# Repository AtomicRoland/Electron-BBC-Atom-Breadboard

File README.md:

# Electron-BBC-Atom-Breadboard
For simple circuits or just for testing purposes you can use this bread board for the Acorn Electron (via a Plus1 cartridge slot) or the BBC / Master / Atom (with 1 MHz bus conversion board). The board has four banks of five rows with 36 pins each.

There are connections between the User port socket and user port holes, between the 1 MHz bus socket and the 1 MHz bus holes and between the edge connector and the 44 holes for the Electron Plus1 cartridge slot.
Optionally you can add a 44 pin header so the board can be connected to the Electron break-out and riser board (but this generally only works reliable for I/O devices running at 1 MHz; ROMS accessed at 2 MHz might fail). Also eight SMD leds with series resistors can be added. The leds are not connected to Vcc or GND so you can use both active high and active low levels to control the leds. 

Of course you can also use this break out board without the female header strips to build a permanent circuit if you have a simple design in mind. That save you the trouble of creating a printed circuit board.
                                                 
*Please unzip the myelin-kicad.pretty-master.zip file before opening the project in KiCad*

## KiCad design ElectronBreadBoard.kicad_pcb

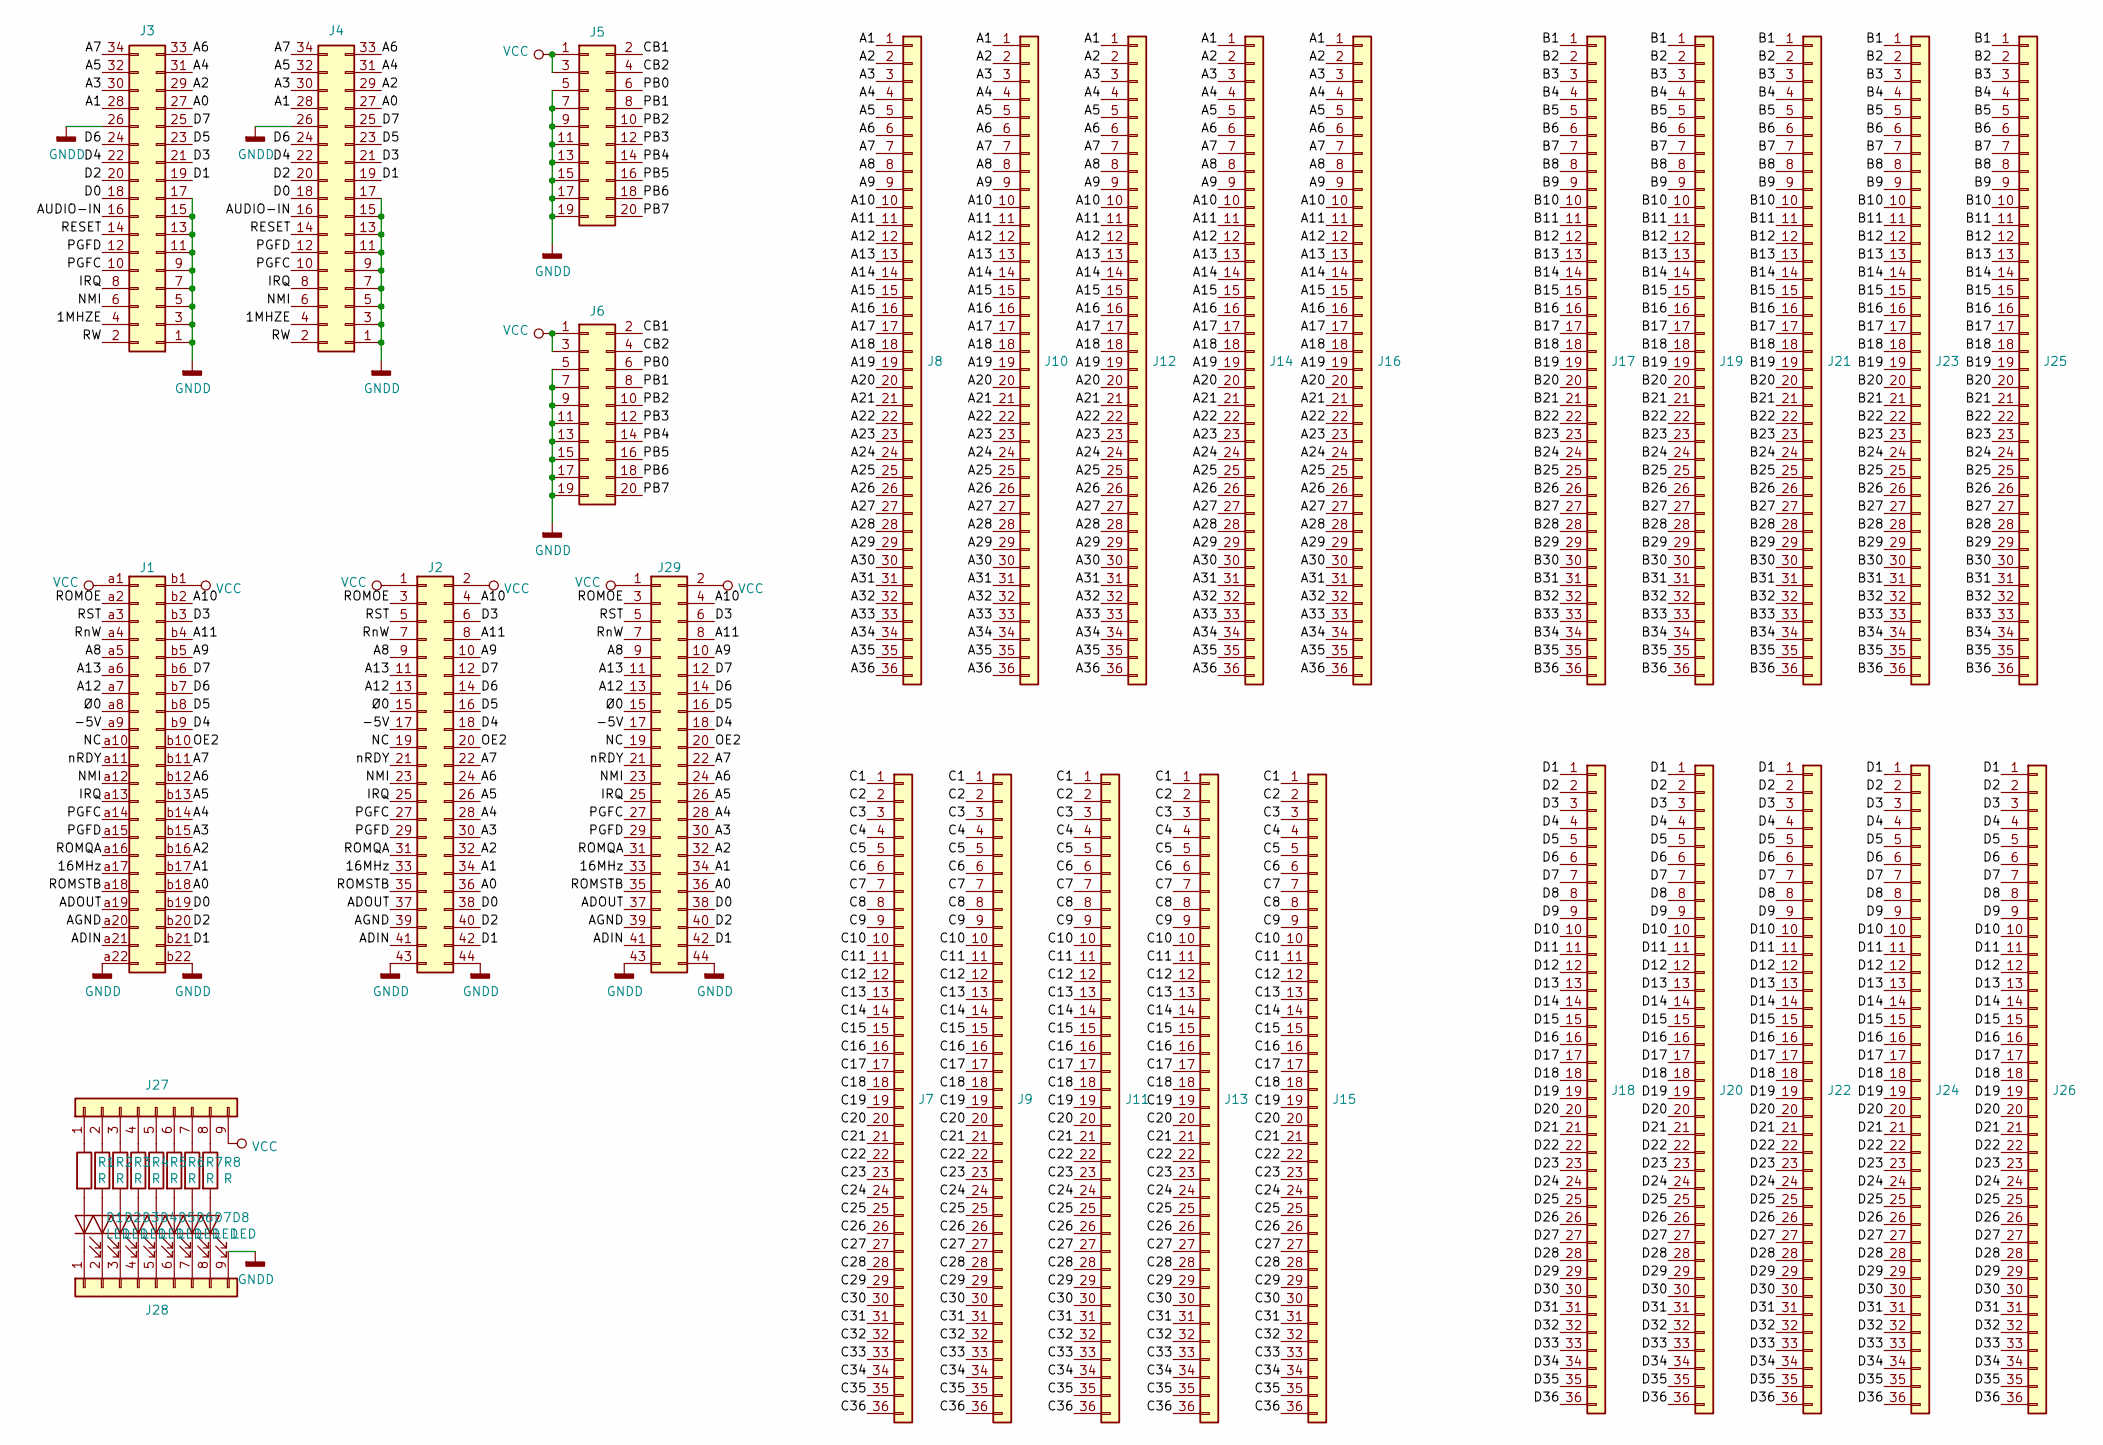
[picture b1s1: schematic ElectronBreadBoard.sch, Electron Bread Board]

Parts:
D1, D2, D3, D4, D5, D6, D7, D8: LED; D_1206_3216Metric_Pad1.42x1.75mm_HandSolder
J1: Conn_02x22_Row_Letter_First; acorn_electron_cartridge_edge_connector
J2, J29: Conn_02x22_Odd_Even; PinHeader_2x22_P2.54mm_Vertical
J3, J4: Conn_02x17_Odd_Even; PinHeader_2x17_P2.54mm_Vertical
J5, J6: Conn_02x10_Odd_Even; PinHeader_2x10_P2.54mm_Vertical
J7, J8, J9, J10, J11, J12, J13, J14, J15, J16, J17, J18, J19, J20, J21, J22, J23, J24, J25, J26: Conn_01x36; PinHeader_1x36_P2.54mm_Vertical
J27, J28: Conn_01x09; PinHeader_1x09_P2.54mm_Vertical
R1, R2, R3, R4, R5, R6, R7, R8: R; R_1206_3216Metric_Pad1.42x1.75mm_HandSolder

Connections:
/1MHZE: J3.4, J4.4
/16MHz: J1.a17, J2.33, J29.33
/-5V: J1.a9, J2.17, J29.17
/A0: J1.b18, J2.36, J3.27, J4.27, J29.36
/A1: J1.b17, J2.34, J3.28, J4.28, J8.1, J10.1, J12.1, J14.1, J16.1, J29.34
/A2: J1.b16, J2.32, J3.29, J4.29, J8.2, J10.2, J12.2, J14.2, J16.2, J29.32
/A3: J1.b15, J2.30, J3.30, J4.30, J8.3, J10.3, J12.3, J14.3, J16.3, J29.30
/A4: J1.b14, J2.28, J3.31, J4.31, J8.4, J10.4, J12.4, J14.4, J16.4, J29.28
/A5: J1.b13, J2.26, J3.32, J4.32, J8.5, J10.5, J12.5, J14.5, J16.5, J29.26
/A6: J1.b12, J2.24, J3.33, J4.33, J8.6, J10.6, J12.6, J14.6, J16.6, J29.24
/A7: J1.b11, J2.22, J3.34, J4.34, J8.7, J10.7, J12.7, J14.7, J16.7, J29.22
/A8: J1.a5, J2.9, J8.8, J10.8, J12.8, J14.8, J16.8, J29.9
/A9: J1.b5, J2.10, J8.9, J10.9, J12.9, J14.9, J16.9, J29.10
/A10: J1.b2, J2.4, J8.10, J10.10, J12.10, J14.10, J16.10, J29.4
/A11: J1.b4, J2.8, J8.11, J10.11, J12.11, J14.11, J16.11, J29.8
/A12: J1.a7, J2.13, J8.12, J10.12, J12.12, J14.12, J16.12, J29.13
/A13: J1.a6, J2.11, J8.13, J10.13, J12.13, J14.13, J16.13, J29.11
/A14: J8.14, J10.14, J12.14, J14.14, J16.14
/A15: J8.15, J10.15, J12.15, J14.15, J16.15
/A16: J8.16, J10.16, J12.16, J14.16, J16.16
/A17: J8.17, J10.17, J12.17, J14.17, J16.17
/A18: J8.18, J10.18, J12.18, J14.18, J16.18
/A19: J8.19, J10.19, J12.19, J14.19, J16.19
/A20: J8.20, J10.20, J12.20, J14.20, J16.20
/A21: J8.21, J10.21, J12.21, J14.21, J16.21
/A22: J8.22, J10.22, J12.22, J14.22, J16.22
/A23: J8.23, J10.23, J12.23, J14.23, J16.23
/A24: J8.24, J10.24, J12.24, J14.24, J16.24
/A25: J8.25, J10.25, J12.25, J14.25, J16.25
/A26: J8.26, J10.26, J12.26, J14.26, J16.26
/A27: J8.27, J10.27, J12.27, J14.27, J16.27
/A28: J8.28, J10.28, J12.28, J14.28, J16.28
/A29: J8.29, J10.29, J12.29, J14.29, J16.29
/A30: J8.30, J10.30, J12.30, J14.30, J16.30
/A31: J8.31, J10.31, J12.31, J14.31, J16.31
/A32: J8.32, J10.32, J12.32, J14.32, J16.32
/A33: J8.33, J10.33, J12.33, J14.33, J16.33
/A34: J8.34, J10.34, J12.34, J14.34, J16.34
/A35: J8.35, J10.35, J12.35, J14.35, J16.35
/A36: J8.36, J10.36, J12.36, J14.36, J16.36
/ADIN: J1.a21, J2.41, J29.41
/ADOUT: J1.a19, J2.37, J29.37
/AGND: J1.a20, J2.39, J29.39
/AUDIO-IN: J3.16, J4.16
/B1: J17.1, J19.1, J21.1, J23.1, J25.1
/B2: J17.2, J19.2, J21.2, J23.2, J25.2
/B3: J17.3, J19.3, J21.3, J23.3, J25.3
/B4: J17.4, J19.4, J21.4, J23.4, J25.4
/B5: J17.5, J19.5, J21.5, J23.5, J25.5
/B6: J17.6, J19.6, J21.6, J23.6, J25.6
/B7: J17.7, J19.7, J21.7, J23.7, J25.7
/B8: J17.8, J19.8, J21.8, J23.8, J25.8
/B9: J17.9, J19.9, J21.9, J23.9, J25.9
/B10: J17.10, J19.10, J21.10, J23.10, J25.10
/B11: J17.11, J19.11, J21.11, J23.11, J25.11
/B12: J17.12, J19.12, J21.12, J23.12, J25.12
/B13: J17.13, J19.13, J21.13, J23.13, J25.13
/B14: J17.14, J19.14, J21.14, J23.14, J25.14
/B15: J17.15, J19.15, J21.15, J23.15, J25.15
/B16: J17.16, J19.16, J21.16, J23.16, J25.16
/B17: J17.17, J19.17, J21.17, J23.17, J25.17
/B18: J17.18, J19.18, J21.18, J23.18, J25.18
/B19: J17.19, J19.19, J21.19, J23.19, J25.19
/B20: J17.20, J19.20, J21.20, J23.20, J25.20
/B21: J17.21, J19.21, J21.21, J23.21, J25.21
/B22: J17.22, J19.22, J21.22, J23.22, J25.22
/B23: J17.23, J19.23, J21.23, J23.23, J25.23
/B24: J17.24, J19.24, J21.24, J23.24, J25.24
/B25: J17.25, J19.25, J21.25, J23.25, J25.25
/B26: J17.26, J19.26, J21.26, J23.26, J25.26
/B27: J17.27, J19.27, J21.27, J23.27, J25.27
/B28: J17.28, J19.28, J21.28, J23.28, J25.28
/B29: J17.29, J19.29, J21.29, J23.29, J25.29
/B30: J17.30, J19.30, J21.30, J23.30, J25.30
/B31: J17.31, J19.31, J21.31, J23.31, J25.31
/B32: J17.32, J19.32, J21.32, J23.32, J25.32
/B33: J17.33, J19.33, J21.33, J23.33, J25.33
/B34: J17.34, J19.34, J21.34, J23.34, J25.34
/B35: J17.35, J19.35, J21.35, J23.35, J25.35
/B36: J17.36, J19.36, J21.36, J23.36, J25.36
/C1: J7.1, J9.1, J11.1, J13.1, J15.1
/C2: J7.2, J9.2, J11.2, J13.2, J15.2
/C3: J7.3, J9.3, J11.3, J13.3, J15.3
/C4: J7.4, J9.4, J11.4, J13.4, J15.4
/C5: J7.5, J9.5, J11.5, J13.5, J15.5
/C6: J7.6, J9.6, J11.6, J13.6, J15.6
/C7: J7.7, J9.7, J11.7, J13.7, J15.7
/C8: J7.8, J9.8, J11.8, J13.8, J15.8
/C9: J7.9, J9.9, J11.9, J13.9, J15.9
/C10: J7.10, J9.10, J11.10, J13.10, J15.10
/C11: J7.11, J9.11, J11.11, J13.11, J15.11
/C12: J7.12, J9.12, J11.12, J13.12, J15.12
/C13: J7.13, J9.13, J11.13, J13.13, J15.13
/C14: J7.14, J9.14, J11.14, J13.14, J15.14
/C15: J7.15, J9.15, J11.15, J13.15, J15.15
/C16: J7.16, J9.16, J11.16, J13.16, J15.16
/C17: J7.17, J9.17, J11.17, J13.17, J15.17
/C18: J7.18, J9.18, J11.18, J13.18, J15.18
/C19: J7.19, J9.19, J11.19, J13.19, J15.19
/C20: J7.20, J9.20, J11.20, J13.20, J15.20
/C21: J7.21, J9.21, J11.21, J13.21, J15.21
/C22: J7.22, J9.22, J11.22, J13.22, J15.22
/C23: J7.23, J9.23, J11.23, J13.23, J15.23
/C24: J7.24, J9.24, J11.24, J13.24, J15.24
/C25: J7.25, J9.25, J11.25, J13.25, J15.25
/C26: J7.26, J9.26, J11.26, J13.26, J15.26
/C27: J7.27, J9.27, J11.27, J13.27, J15.27
/C28: J7.28, J9.28, J11.28, J13.28, J15.28
/C29: J7.29, J9.29, J11.29, J13.29, J15.29
/C30: J7.30, J9.30, J11.30, J13.30, J15.30
/C31: J7.31, J9.31, J11.31, J13.31, J15.31
/C32: J7.32, J9.32, J11.32, J13.32, J15.32
/C33: J7.33, J9.33, J11.33, J13.33, J15.33
/C34: J7.34, J9.34, J11.34, J13.34, J15.34
/C35: J7.35, J9.35, J11.35, J13.35, J15.35
/C36: J7.36, J9.36, J11.36, J13.36, J15.36
/CB1: J5.2, J6.2
/CB2: J5.4, J6.4
/D0: J1.b19, J2.38, J3.18, J4.18, J29.38
/D1: J1.b21, J2.42, J3.19, J4.19, J18.1, J20.1, J22.1, J24.1, J26.1, J29.42
/D2: J1.b20, J2.40, J3.20, J4.20, J18.2, J20.2, J22.2, J24.2, J26.2, J29.40
/D3: J1.b3, J2.6, J3.21, J4.21, J18.3, J20.3, J22.3, J24.3, J26.3, J29.6
/D4: J1.b9, J2.18, J3.22, J4.22, J18.4, J20.4, J22.4, J24.4, J26.4, J29.18
/D5: J1.b8, J2.16, J3.23, J4.23, J18.5, J20.5, J22.5, J24.5, J26.5, J29.16
/D6: J1.b7, J2.14, J3.24, J4.24, J18.6, J20.6, J22.6, J24.6, J26.6, J29.14
/D7: J1.b6, J2.12, J3.25, J4.25, J18.7, J20.7, J22.7, J24.7, J26.7, J29.12
/D8: J18.8, J20.8, J22.8, J24.8, J26.8
/D9: J18.9, J20.9, J22.9, J24.9, J26.9
/D10: J18.10, J20.10, J22.10, J24.10, J26.10
/D11: J18.11, J20.11, J22.11, J24.11, J26.11
/D12: J18.12, J20.12, J22.12, J24.12, J26.12
/D13: J18.13, J20.13, J22.13, J24.13, J26.13
/D14: J18.14, J20.14, J22.14, J24.14, J26.14
/D15: J18.15, J20.15, J22.15, J24.15, J26.15
/D16: J18.16, J20.16, J22.16, J24.16, J26.16
/D17: J18.17, J20.17, J22.17, J24.17, J26.17
/D18: J18.18, J20.18, J22.18, J24.18, J26.18
/D19: J18.19, J20.19, J22.19, J24.19, J26.19
/D20: J18.20, J20.20, J22.20, J24.20, J26.20
/D21: J18.21, J20.21, J22.21, J24.21, J26.21
/D22: J18.22, J20.22, J22.22, J24.22, J26.22
/D23: J18.23, J20.23, J22.23, J24.23, J26.23
/D24: J18.24, J20.24, J22.24, J24.24, J26.24
/D25: J18.25, J20.25, J22.25, J24.25, J26.25
/D26: J18.26, J20.26, J22.26, J24.26, J26.26
/D27: J18.27, J20.27, J22.27, J24.27, J26.27
/D28: J18.28, J20.28, J22.28, J24.28, J26.28
/D29: J18.29, J20.29, J22.29, J24.29, J26.29
/D30: J18.30, J20.30, J22.30, J24.30, J26.30
/D31: J18.31, J20.31, J22.31, J24.31, J26.31
/D32: J18.32, J20.32, J22.32, J24.32, J26.32
/D33: J18.33, J20.33, J22.33, J24.33, J26.33
/D34: J18.34, J20.34, J22.34, J24.34, J26.34
/D35: J18.35, J20.35, J22.35, J24.35, J26.35
/D36: J18.36, J20.36, J22.36, J24.36, J26.36
/IRQ: J1.a13, J2.25, J3.8, J4.8, J29.25
/NC: J1.a10, J2.19, J29.19
/NMI: J1.a12, J2.23, J3.6, J4.6, J29.23
/OE2: J1.b10, J2.20, J29.20
/PB0: J5.6, J6.6
/PB1: J5.8, J6.8
/PB2: J5.10, J6.10
/PB3: J5.12, J6.12
/PB4: J5.14, J6.14
/PB5: J5.16, J6.16
/PB6: J5.18, J6.18
/PB7: J5.20, J6.20
/PGFC: J1.a14, J2.27, J3.10, J4.10, J29.27
/PGFD: J1.a15, J2.29, J3.12, J4.12, J29.29
/RESET: J3.14, J4.14
/ROMOE: J1.a2, J2.3, J29.3
/ROMQA: J1.a16, J2.31, J29.31
/ROMSTB: J1.a18, J2.35, J29.35
/RST: J1.a3, J2.5, J29.5
/RW: J3.2, J4.2
/RnW: J1.a4, J2.7, J29.7
/nRDY: J1.a11, J2.21, J29.21
/Ø0: J1.a8, J2.15, J29.15
GNDD: J1.a22, J1.b22, J2.43, J2.44, J3.1, J3.3, J3.5, J3.7, J3.9, J3.11, J3.13, J3.15, J3.17, J3.26, J4.1, J4.3, J4.5, J4.7, J4.9, J4.11, J4.13, J4.15, J4.17, J4.26, J5.5, J5.7, J5.9, J5.11, J5.13, J5.15, J5.17, J5.19, J6.5, J6.7, J6.9, J6.11, J6.13, J6.15, J6.17, J6.19, J28.9, J29.43, J29.44
unnamed: D1.1 (K), J28.1
unnamed: D1.2 (A), R1.2
unnamed: D2.1 (K), J28.2
unnamed: D2.2 (A), R2.2
unnamed: D3.1 (K), J28.3
unnamed: D3.2 (A), R3.2
unnamed: D4.1 (K), J28.4
unnamed: D4.2 (A), R4.2
unnamed: D5.1 (K), J28.5
unnamed: D5.2 (A), R5.2
unnamed: D6.1 (K), J28.6
unnamed: D6.2 (A), R6.2
unnamed: D7.1 (K), J28.7
unnamed: D7.2 (A), R7.2
unnamed: D8.1 (K), J28.8
unnamed: D8.2 (A), R8.2
unnamed: J27.1, R1.1
unnamed: J27.2, R2.1
unnamed: J27.3, R3.1
unnamed: J27.4, R4.1
unnamed: J27.5, R5.1
unnamed: J27.6, R6.1
unnamed: J27.7, R7.1
unnamed: J27.8, R8.1
VCC: J1.a1, J1.b1, J2.1, J2.2, J5.1, J5.3, J6.1, J6.3, J27.9, J29.1, J29.2

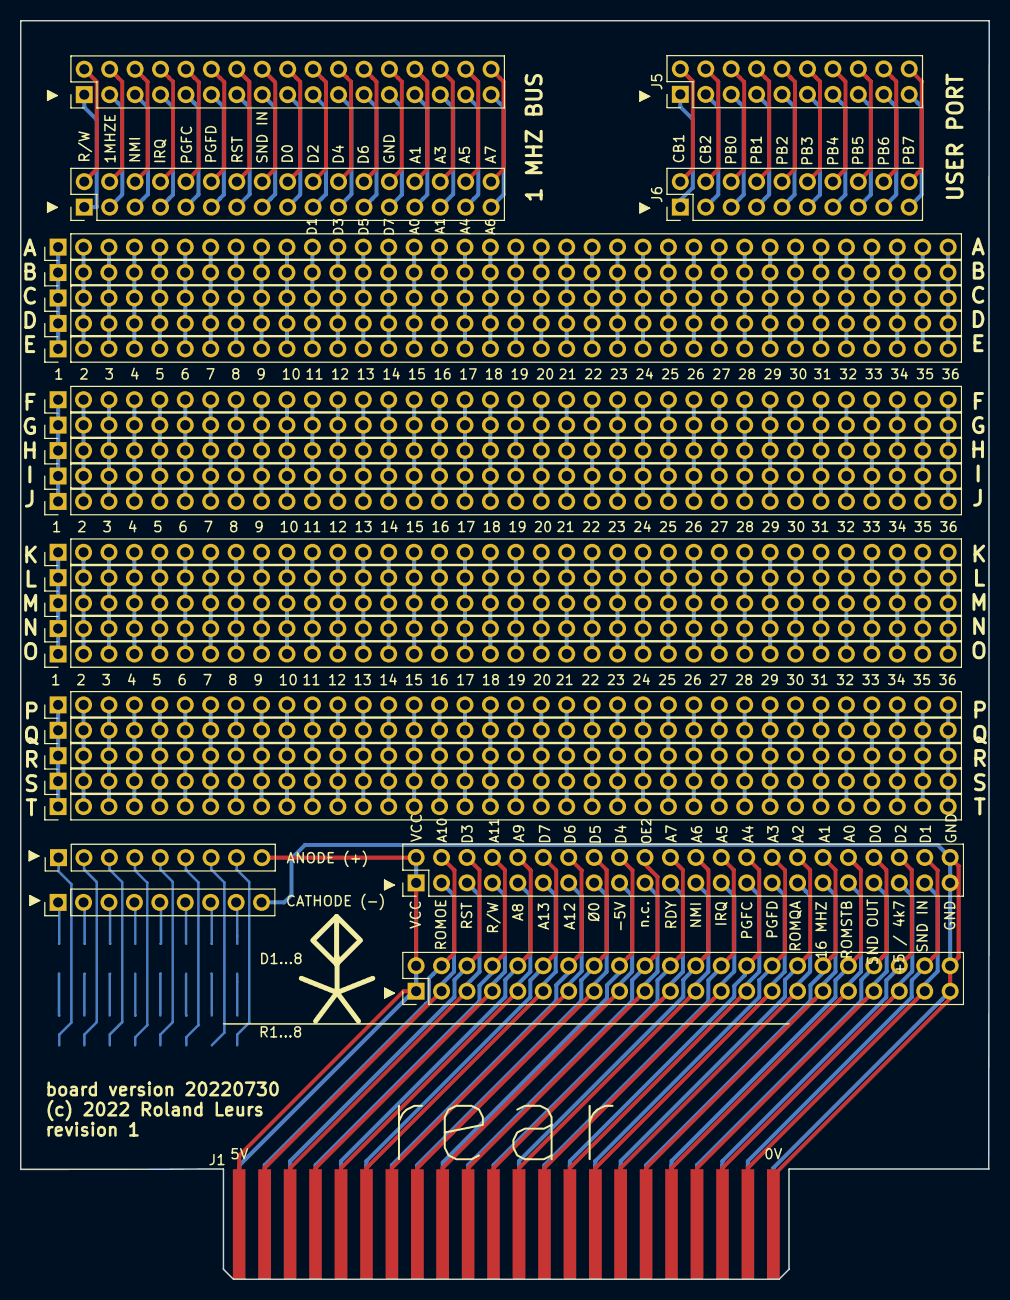
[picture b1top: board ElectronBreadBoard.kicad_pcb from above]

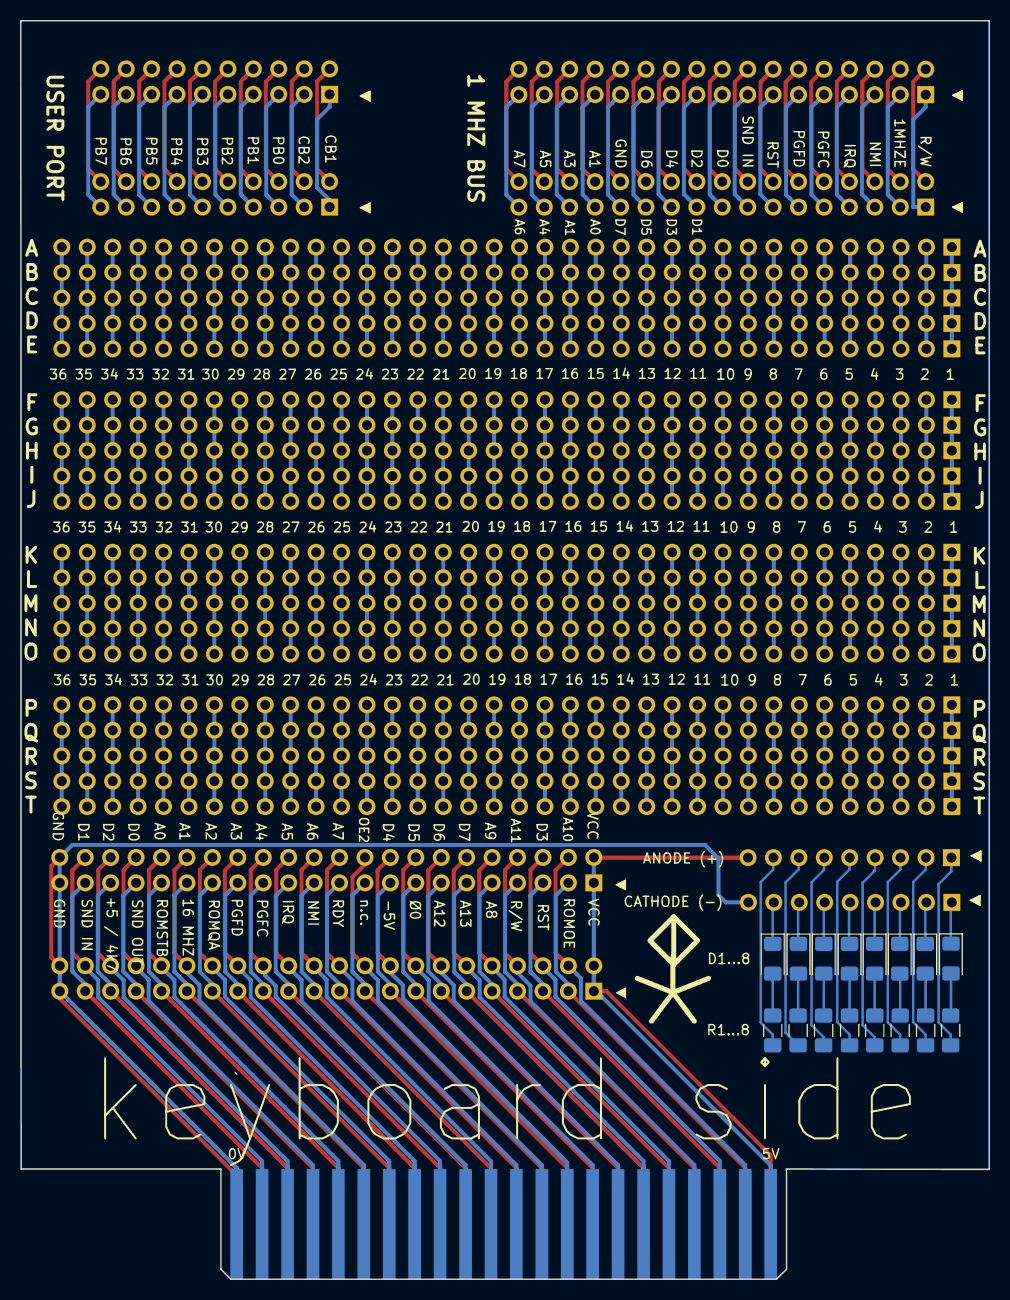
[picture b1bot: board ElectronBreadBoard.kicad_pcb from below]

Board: 2 copper layers, 96.7 x 125.7 mm, 45 parts (16 on the bottom side), 204 nets.

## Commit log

2022-08-28 Initial upload to repository of MK1

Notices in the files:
ElectronBreadBoard.kicad_pcb:
(c) 2022 Roland Leurs
